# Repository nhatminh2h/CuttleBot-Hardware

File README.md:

# CuttleBot and FOLD Actuator Electronics Design
This repository contains the electronics design files and firmware for the CuttleBot, a biomimetic underwater robot, and its FOLD actuators. The system architecture is designed for efficient control and feedback, providing precise manipulation of the actuators for underwater mobility.

A follow up work from [Fin ray-inspired, Origami, Small Scale Actuator for Fin Manipulation in Aquatic Bioinspired Robots](https://arxiv.org/abs/2407.16821)

---

## System Overview

The CuttleBot's electronic system is divided into two key components:
1. **Main Controller**
2. **Driver and Actuator Modules (8 units)**

---

## Components

### Main Controller (Current version: v1.1)

- **Microcontroller**: STM32H743VHX
- **Connected Sensors**:
  - **IMU**: Three sensors (ASM330LHHXG1, ICM20602, ICM20602) are connected over SPI to provide Attitude and Heading Reference System (AHRS) data for underwater navigation.
  - **Pressure Sensor**: MPRLS0025PA 00001A, used to determine depth.
  - **Flash Memory**: W25Q256/VEIQ TR, for data storage.

The main controller (STM32H743VHX) processes data from the IMUs and the pressure sensor to calculate the robot's position and orientation. It then broadcasts the actuator position setpoints over I2C to each of the driver modules.

### Driver Module (8 units)

Each FOLD actuator has its own dedicated driver module, responsible for controlling the actuator's motion and maintaining position feedback. The driver module is built around the following components:

- **Microcontroller**: STM32F031G6U6
  - Stores lookup tables for position control and uses feedback from the Hall sensor to control actuator position.
  
- **Hall Sensor**: DRV5055
  - Provides position feedback to the driver, enabling precise control of actuator movement.

- **Motor Driver (H-Bridge)**: DRV8231A
  - Drives the actuator with current limiting up to 2.2A, allowing bidirectional motor control.
  - Receives control signals from the driver microcontroller.

- **Voltage Regulation**: 
  - **LDO (TPS709)** provides a stable 3.3V supply for the driver microcontroller and Hall sensor.
  - Supports a motor voltage range of 5-16V for the H-Bridge.

#### FOLD Actuator

The FOLD actuator is an origami-inspired, electromagnetically driven, tendon-driven actuator. Controlled via the H-Bridge and regulated by position feedback from the Hall sensor, the actuator provides precise biomimetic movement for underwater mobility.

---

### Power and Communication

- **Power**:
  - Each driver module includes an LDO (TPS709) to provide a stable 3.3V for the microcontroller and sensor circuits.
  - The motor voltage can range from 5-16V, which also powers the H-Bridge for actuator control.
  
- **Communication**:
  - **I2C** is used by the main controller to broadcast actuator position setpoints to each driver module.
  - **SPI** communication links the main controller to the IMUs, pressure sensor, and flash memory.

---

### Getting Started

1. **Cloning the Repository**:
   ```bash
   git clone https://github.com/[username]/cuttlebot-electronics.git

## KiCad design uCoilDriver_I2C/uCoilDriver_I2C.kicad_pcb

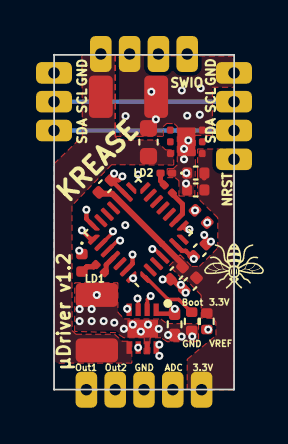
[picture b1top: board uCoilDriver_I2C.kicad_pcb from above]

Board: 4 copper layers, 10.0 x 18.6 mm, 33 parts (0 on the bottom side), 20 nets.

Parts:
C1, C6, C8: 100n; C_0402_1005Metric
C2: 1 uF; C_0603_1608Metric
C3: 2.2 uF; C_0402_1005Metric
C4, C7: 47u; CP_EIA-3528-12_Kemet-T
C5: 4.7 uF; C_0402_1005Metric
C11: 10n; C_0402_1005Metric
C12: 1 uF; C_0402_1005Metric
D1: BLUE LED; LED_0402_1005Metric
D2: BLUE LED; LED_0201_0603Metric
R1: 100k; R_0402_1005Metric
R2: 0; R_0402_1005Metric
R3, R5: 1k5; R_0201_0603Metric
R4: 1k5; R_0402_1005Metric_Pad0.72x0.64mm_HandSolder
TP1, TP2, TP3, TP6, TP7, TP8, TP11, TP12, TP13, TP14, TP15, TP16, TP17: Pad; Castellated_Pad_1x2mm
U1: DRV8231ADSGR; SON50P200X200X80-9N
U2: STM32F031G6Ux; QFN-28_4x4mm_P0.5mm
U3: TPS709; WSON-6-1EP_2x2mm_P0.65mm_EP1x1.6mm

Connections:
+3.3V: C3.1, C5.1, C6.1, C11.1, C12.1, R2.2, TP16.1, U2.5 (VDDA), U2.17 (VDD), U3.1 (OUT)
+12V: C2.1, C4.1, C7.1, TP1.1, U1.5 (VM), U3.6 (IN)
/ADC_IN: C8.1, TP17.1, U2.6 (PA0)
/I2C1_SCL: TP8.1, U2.27 (PB6)
/I2C1_SDA: TP7.1, U2.28 (PB7)
/NRST: C1.1, TP6.1, U2.4 (NRST)
/OUT1: TP13.1, U1.6 (OUT1)
/OUT2: TP14.1, U1.8 (OUT2)
/PA2_IPROPI: R4.2, U1.1 (IPROPI), U2.8 (PA2)
/SWCLK: TP3.1, U2.22 (PA14)
/SWDIO: TP12.1, U2.21 (PA13)
/TIM2_CH1: U1.3 (IN1), U2.23 (PA15)
/TIM2_CH2: U1.2 (IN2), U2.24 (PB3)
GND: C1.2, C2.2, C3.2, C4.2, C5.2, C6.2, C7.2, C8.2, C11.2, C12.2, D1.1 (K), D2.1 (K), R1.1, R4.1, TP2.1, TP11.1, TP15.1, U1.7 (GND_1), U1.9 (GND_2), U2.16 (VSS), U3.3 (GND), U3.7 (GND)
unnamed: D1.2 (A), R3.1
unnamed: D2.2 (A), R5.1
unnamed: R2.1, U1.4 (VREF)
unnamed: R1.2, U2.1 (BOOT0)
unnamed: R5.2, U2.9 (PA3)
unnamed: R3.2, U2.25 (PB4)

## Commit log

2024-10-30 Initial. Organised PCB design files
2024-10-30 Updated images
2024-10-30 Fix block diagram
